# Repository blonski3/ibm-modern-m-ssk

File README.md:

# IBM Model M SSK Wireless
*Opracowanie i wykonanie układu sterującego klawiaturą mechaniczną*. Bezprzewodowa modernizacja IBM Model M SSK: nRF52840 + nPM1300, własna membrana FPC z diodą na klawisz, firmware ZMK.

## Struktura repozytorium

```
hardware/controller/   projekt KiCad 10: motherboard + daughterboard (jedna PCB, DB wyłamywany)
hardware/membrane/     projekt KiCad 10: membrana FPC, schemat matrycy 6 × 17 i obrys bazowy
hardware/membrane-row/ folia ROW (górna, 2 warstwy, diody), wersja zamówiona 2026-11-23
hardware/membrane-col/ folia COL (dolna, 1 warstwa), wersja zamówiona 2026-11-23
hardware/lib/          wspólna biblioteka: symbole, footprinty, modele 3D
production/            zamrożone paczki zamówień (controller/revA-2026-11-16: Gerbery, BOM, CPL; membrane/2026-11-23: Gerbery folii)
docs/                  CHANGELOG.md, HARDWARE_DECISIONS.md, datasheets/, diagrams/
mechanics/             pomiary i eksporty z Onshape
reference/             projekty referencyjne (Nordic, FSSK v1.00)
tools/                 własne wtyczki KiCada (*-o-matic, via-o-tronic) i skrypty (kicad-check.sh, check_3d_paths.py); indeks w tools/README.md
```

Decyzje projektowe i ich uzasadnienia: `docs/HARDWARE_DECISIONS.md`; historia zmian: `docs/CHANGELOG.md`.

## Resources

[Bolt Mod, A Comprehensive Tutorial: IBM Model M SSK 1991](https://imgur.com/gallery/bolt-mod-comprehensive-tutorial-ibm-model-m-ssk-1991-arUYken)

[FSSK v1.00 - Installation & Users Manual](https://deskthority.net/viewtopic.php?t=13551)

[Request for Permission to Integrate Zephyr PF1550 PMIC Drivers into ZMK #2958](https://github.com/zmkfirmware/zmk/issues/2958)

[nRF52840 Product Specification v1.5](https://docs.nordicsemi.com/viewer/book-attachment/de~7rocmcN70bRHnA4~zJA/H1GC97m6GZQEaMxKCN6OOg-de~7rocmcN70bRHnA4~zJA)

[nPM1300 Product Specification v1.3](https://docs.nordicsemi.com/viewer/book-attachment/ZO1FVHHS04YNNMSlbsZ0Kg/KbFbu1gXgIMOyTgBK7q46A-ZO1FVHHS04YNNMSlbsZ0Kg)

[Keyboard Layout Editor NG - IBM Model M](https://editor.keyboard-tools.xyz/#share=NobwRAhgrgLgFgewE5gFxgEYBsEDswA0YuEAtgKZpgCSAQgLIAEAyswNKP0IAm5WnhMAGcADhADGAS1wBzAPoBPNACYADADoAHABYAvgVCQ0q-WELgAHmgCMpwfaLmwV1BoCsdx17MFLx9R7eDj5+rgGePmYAugbgSqi2QUmRwanJDqHW4ekxhgDuNtkp6SXFZU4FCUVOLu4R9rnglVkA7IHlpWkdTSrqyu1gjWCVyn0DnRPFPVVtnqGjA0PN1b7ONkTL49Mtc8OFW2sJG-u7tSspQy7Wo21E8QC0AMy7y-12S4VvQUMPysdVi1ih2sekclxs2juaHuoOiUSAA)

[WR-PHD Pin Header drawing](https://www.we-online.com/components/products/datasheet/61300811021.pdf)

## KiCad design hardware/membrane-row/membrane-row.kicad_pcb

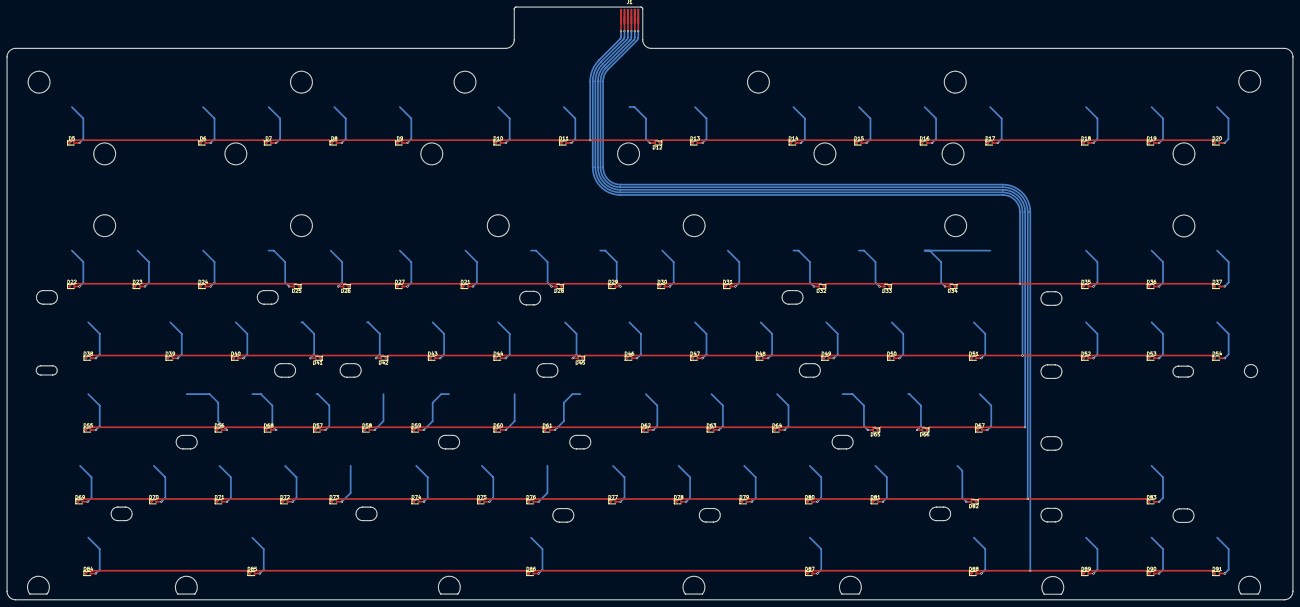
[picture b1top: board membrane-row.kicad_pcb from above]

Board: 2 copper layers, 373.4 x 172.1 mm, 176 parts (0 on the bottom side), 93 nets.

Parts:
D5, D6, D7, D8, D9, D10, D11, D12, D13, D14, D15, D16, D17, D18, D19, D20, D21, D22, D23, D24, D25, D26, D27, D28, D29, D30, D31, D32, D33, D34, D35, D36, D37, D38, D39, D40, D41, D42, D43, D44, D45, D46, D47, D48, D49, D50, D51, D52, D53, D54, D55, D56, D57, D58, D59, D60, D61, D62, D63, D64, D65, D66, D67, D68, D69, D70, D71, D72, D73, D74, D75, D76, D77, D78, D79, D80, D81, D82, D83, D84, D85, D86, D87, D88, D89, D90, D91: D_Small_Filled; D_SOD-523
J1: Conn_01x06; FFC_solder_6P_P1.00
SW1: Esc; ibm_bs_1u_row
SW2: F1; ibm_bs_1u_row
SW3: F2; ibm_bs_1u_row
SW4: F3; ibm_bs_1u_row
SW5: F4; ibm_bs_1u_row
SW6: F5; ibm_bs_1u_row
SW7: F6; ibm_bs_1u_row
SW8: F7; ibm_bs_1u_row
SW9: F8; ibm_bs_1u_row
SW10: F9; ibm_bs_1u_row
SW11: F10; ibm_bs_1u_row
SW12: F11; ibm_bs_1u_row
SW13: F12; ibm_bs_1u_row
SW14: PrintScreen; ibm_bs_1u_row
SW15: ScrollLock; ibm_bs_1u_row
SW16: PauseBreak; ibm_bs_1u_row
SW17, SW31: Backspace; ibm_bs_1u_row
SW18: ibm_bs_1u_row
SW19: 1; ibm_bs_1u_row
SW20: 2; ibm_bs_1u_row
SW21: 3; ibm_bs_1u_row
SW22: 4; ibm_bs_1u_row
SW23: 5; ibm_bs_1u_row
SW24: 6; ibm_bs_1u_row
SW25: 7; ibm_bs_1u_row
SW26: 8; ibm_bs_1u_row
SW27: 9; ibm_bs_1u_row
SW28: 0; ibm_bs_1u_row
SW29: -; ibm_bs_1u_row
SW30: =; ibm_bs_1u_row
SW32: Insert; ibm_bs_1u_row
SW33: Home; ibm_bs_1u_row
SW34: PgUp; ibm_bs_1u_row
SW35: Tab; ibm_bs_1u_row
SW36: Q; ibm_bs_1u_row
SW37: W; ibm_bs_1u_row
SW38: E; ibm_bs_1u_row
SW39: R; ibm_bs_1u_row
SW40: T; ibm_bs_1u_row
SW41: Y; ibm_bs_1u_row
SW42: U; ibm_bs_1u_row
SW43: I; ibm_bs_1u_row
SW44: O; ibm_bs_1u_row
SW45: P; ibm_bs_1u_row
SW46: [; ibm_bs_1u_row
SW47: ]; ibm_bs_1u_row
SW48: \; ibm_bs_1u_row
SW49: Delete; ibm_bs_1u_row
SW50: End; ibm_bs_1u_row
SW51: PgDw; ibm_bs_1u_row
SW52: CapsLock; ibm_bs_1u_row
SW53: A; ibm_bs_1u_row
SW54: S; ibm_bs_1u_row
SW55: D; ibm_bs_1u_row
SW56: F; ibm_bs_1u_row
SW57: G; ibm_bs_1u_row
SW58: H; ibm_bs_1u_row
SW59: J; ibm_bs_1u_row
SW60: K; ibm_bs_1u_row
SW61: L; ibm_bs_1u_row
SW62: ;; ibm_bs_1u_row
SW63: '; ibm_bs_1u_row
SW64, SW67: \ ISO; ibm_bs_1u_row
SW65: Enter; ibm_bs_1u_row
SW66: LShift; ibm_bs_1u_row
SW68: Z; ibm_bs_1u_row
SW69: X; ibm_bs_1u_row
SW70: C; ibm_bs_1u_row
SW71: V; ibm_bs_1u_row
SW72: B; ibm_bs_1u_row
SW73: N; ibm_bs_1u_row
SW74: M; ibm_bs_1u_row
SW75: ,; ibm_bs_1u_row
SW76: .; ibm_bs_1u_row
SW77: /; ibm_bs_1u_row
SW78: RShift (???); ibm_bs_1u_row
SW79: RShift; ibm_bs_1u_row
SW80: Up; ibm_bs_1u_row
SW81: LCtrl; ibm_bs_1u_row
SW82: LAlt; ibm_bs_1u_row
SW83: Space; ibm_bs_1u_row
SW84: RAlt; ibm_bs_1u_row
SW85: RCtrl; ibm_bs_1u_row
SW86: Left; ibm_bs_1u_row
SW87: Down; ibm_bs_1u_row
SW88: Right; ibm_bs_1u_row

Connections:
/ROW0: D5.1 (K), D6.1 (K), D7.1 (K), D8.1 (K), D9.1 (K), D10.1 (K), D11.1 (K), D12.1 (K), D13.1 (K), D14.1 (K), D15.1 (K), D16.1 (K), D17.1 (K), D18.1 (K), D19.1 (K), D20.1 (K), J1.6
/ROW1: D21.1 (K), D22.1 (K), D23.1 (K), D24.1 (K), D25.1 (K), D26.1 (K), D27.1 (K), D28.1 (K), D29.1 (K), D30.1 (K), D31.1 (K), D32.1 (K), D33.1 (K), D34.1 (K), D35.1 (K), D36.1 (K), D37.1 (K), J1.5
/ROW2: D38.1 (K), D39.1 (K), D40.1 (K), D41.1 (K), D42.1 (K), D43.1 (K), D44.1 (K), D45.1 (K), D46.1 (K), D47.1 (K), D48.1 (K), D49.1 (K), D50.1 (K), D51.1 (K), D52.1 (K), D53.1 (K), D54.1 (K), J1.4
/ROW3: D55.1 (K), D56.1 (K), D57.1 (K), D58.1 (K), D59.1 (K), D60.1 (K), D61.1 (K), D62.1 (K), D63.1 (K), D64.1 (K), D65.1 (K), D66.1 (K), D67.1 (K), D68.1 (K), J1.3
/ROW4: D69.1 (K), D70.1 (K), D71.1 (K), D72.1 (K), D73.1 (K), D74.1 (K), D75.1 (K), D76.1 (K), D77.1 (K), D78.1 (K), D79.1 (K), D80.1 (K), D81.1 (K), D82.1 (K), D83.1 (K), J1.2
/ROW5: D84.1 (K), D85.1 (K), D86.1 (K), D87.1 (K), D88.1 (K), D89.1 (K), D90.1 (K), D91.1 (K), J1.1
unnamed: D5.2 (A), SW1.1 (1_1)
unnamed: D6.2 (A), SW2.1 (1_1)
unnamed: D7.2 (A), SW3.1 (1_1)
unnamed: D8.2 (A), SW4.1 (1_1)
unnamed: D9.2 (A), SW5.1 (1_1)
unnamed: D10.2 (A), SW6.1 (1_1)
unnamed: D11.2 (A), SW7.1 (1_1)
unnamed: D12.2 (A), SW8.1 (1_1)
unnamed: D13.2 (A), SW9.1 (1_1)
unnamed: D14.2 (A), SW10.1 (1_1)
unnamed: D15.2 (A), SW11.1 (1_1)
unnamed: D16.2 (A), SW12.1 (1_1)
unnamed: D17.2 (A), SW13.1 (1_1)
unnamed: D18.2 (A), SW14.1 (1_1)
unnamed: D19.2 (A), SW15.1 (1_1)
unnamed: D20.2 (A), SW16.1 (1_1)
unnamed: D21.2 (A), SW24.1 (1_1)
unnamed: D22.2 (A), SW18.1 (1_1)
unnamed: D23.2 (A), SW19.1 (1_1)
unnamed: D24.2 (A), SW20.1 (1_1)
unnamed: D25.2 (A), SW21.1 (1_1)
unnamed: D26.2 (A), SW22.1 (1_1)
unnamed: D27.2 (A), SW23.1 (1_1)
unnamed: D28.2 (A), SW25.1 (1_1)
unnamed: D29.2 (A), SW26.1 (1_1)
unnamed: D30.2 (A), SW27.1 (1_1)
unnamed: D31.2 (A), SW28.1 (1_1)
unnamed: D32.2 (A), SW29.1 (1_1)
unnamed: D33.2 (A), SW30.1 (1_1)
unnamed: D34.2 (A), SW17.1 (1_1), SW31.1 (1_1)
unnamed: D35.2 (A), SW32.1 (1_1)
unnamed: D36.2 (A), SW33.1 (1_1)
unnamed: D37.2 (A), SW34.1 (1_1)
unnamed: D38.2 (A), SW35.1 (1_1)
unnamed: D39.2 (A), SW36.1 (1_1)
unnamed: D40.2 (A), SW37.1 (1_1)
unnamed: D41.2 (A), SW38.1 (1_1)
unnamed: D42.2 (A), SW39.1 (1_1)
unnamed: D43.2 (A), SW40.1 (1_1)
unnamed: D44.2 (A), SW41.1 (1_1)
unnamed: D45.2 (A), SW42.1 (1_1)
unnamed: D46.2 (A), SW43.1 (1_1)
unnamed: D47.2 (A), SW44.1 (1_1)
unnamed: D48.2 (A), SW45.1 (1_1)
unnamed: D49.2 (A), SW46.1 (1_1)
unnamed: D50.2 (A), SW47.1 (1_1)
unnamed: D51.2 (A), SW48.1 (1_1)
unnamed: D52.2 (A), SW49.1 (1_1)
unnamed: D53.2 (A), SW50.1 (1_1)
unnamed: D54.2 (A), SW51.1 (1_1)
unnamed: D55.2 (A), SW52.1 (1_1)
unnamed: D56.2 (A), SW53.1 (1_1)
unnamed: D57.2 (A), SW55.1 (1_1)
unnamed: D58.2 (A), SW56.1 (1_1)
unnamed: D59.2 (A), SW57.1 (1_1)
unnamed: D60.2 (A), SW58.1 (1_1)
unnamed: D61.2 (A), SW59.1 (1_1)
unnamed: D62.2 (A), SW60.1 (1_1)
unnamed: D63.2 (A), SW61.1 (1_1)
unnamed: D64.2 (A), SW62.1 (1_1)
unnamed: D65.2 (A), SW63.1 (1_1)
unnamed: D66.2 (A), SW64.1 (1_1)
unnamed: D67.2 (A), SW65.1 (1_1)
unnamed: D68.2 (A), SW54.1 (1_1)
unnamed: D69.2 (A), SW66.1 (1_1)
unnamed: D70.2 (A), SW67.1 (1_1)
unnamed: D71.2 (A), SW68.1 (1_1)
unnamed: D72.2 (A), SW69.1 (1_1)
unnamed: D73.2 (A), SW70.1 (1_1)
unnamed: D74.2 (A), SW71.1 (1_1)
unnamed: D75.2 (A), SW72.1 (1_1)
unnamed: D76.2 (A), SW73.1 (1_1)
unnamed: D77.2 (A), SW74.1 (1_1)
unnamed: D78.2 (A), SW75.1 (1_1)
unnamed: D79.2 (A), SW76.1 (1_1)
unnamed: D80.2 (A), SW77.1 (1_1)
unnamed: D81.2 (A), SW78.1 (1_1)
unnamed: D82.2 (A), SW79.1 (1_1)
unnamed: D83.2 (A), SW80.1 (1_1)
unnamed: D84.2 (A), SW81.1 (1_1)
unnamed: D85.2 (A), SW82.1 (1_1)
unnamed: D86.2 (A), SW83.1 (1_1)
unnamed: D87.2 (A), SW84.1 (1_1)
unnamed: D88.2 (A), SW85.1 (1_1)
unnamed: D89.2 (A), SW86.1 (1_1)
unnamed: D90.2 (A), SW87.1 (1_1)
unnamed: D91.2 (A), SW88.1 (1_1)

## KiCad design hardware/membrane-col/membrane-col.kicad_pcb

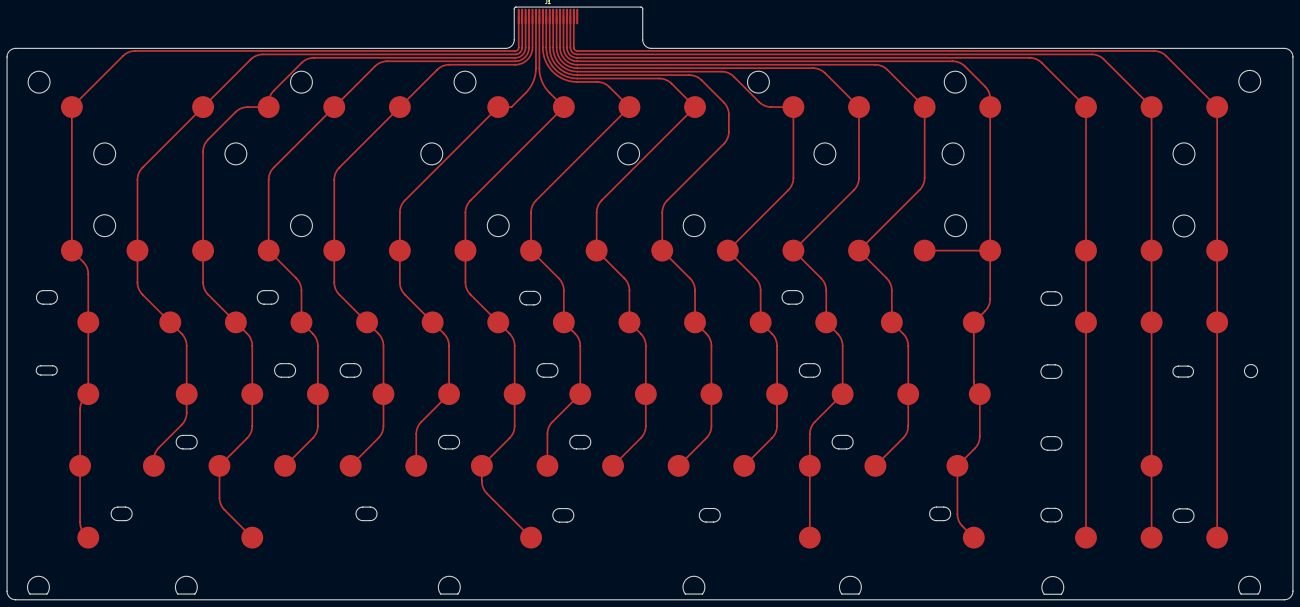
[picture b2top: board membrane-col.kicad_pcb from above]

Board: 2 copper layers, 373.4 x 172.1 mm, 89 parts (0 on the bottom side), 17 nets.

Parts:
J1: Conn_01x06; FFC_solder_18P_P1.00
SW1: Esc; ibm_bs_1u_col
SW2: F1; ibm_bs_1u_col
SW3: F2; ibm_bs_1u_col
SW4: F3; ibm_bs_1u_col
SW5: F4; ibm_bs_1u_col
SW6: F5; ibm_bs_1u_col
SW7: F6; ibm_bs_1u_col
SW8: F7; ibm_bs_1u_col
SW9: F8; ibm_bs_1u_col
SW10: F9; ibm_bs_1u_col
SW11: F10; ibm_bs_1u_col
SW12: F11; ibm_bs_1u_col
SW13: F12; ibm_bs_1u_col
SW14: PrintScreen; ibm_bs_1u_col
SW15: ScrollLock; ibm_bs_1u_col
SW16: PauseBreak; ibm_bs_1u_col
SW17, SW31: Backspace; ibm_bs_1u_col
SW18: ibm_bs_1u_col
SW19: 1; ibm_bs_1u_col
SW20: 2; ibm_bs_1u_col
SW21: 3; ibm_bs_1u_col
SW22: 4; ibm_bs_1u_col
SW23: 5; ibm_bs_1u_col
SW24: 6; ibm_bs_1u_col
SW25: 7; ibm_bs_1u_col
SW26: 8; ibm_bs_1u_col
SW27: 9; ibm_bs_1u_col
SW28: 0; ibm_bs_1u_col
SW29: -; ibm_bs_1u_col
SW30: =; ibm_bs_1u_col
SW32: Insert; ibm_bs_1u_col
SW33: Home; ibm_bs_1u_col
SW34: PgUp; ibm_bs_1u_col
SW35: Tab; ibm_bs_1u_col
SW36: Q; ibm_bs_1u_col
SW37: W; ibm_bs_1u_col
SW38: E; ibm_bs_1u_col
SW39: R; ibm_bs_1u_col
SW40: T; ibm_bs_1u_col
SW41: Y; ibm_bs_1u_col
SW42: U; ibm_bs_1u_col
SW43: I; ibm_bs_1u_col
SW44: O; ibm_bs_1u_col
SW45: P; ibm_bs_1u_col
SW46: [; ibm_bs_1u_col
SW47: ]; ibm_bs_1u_col
SW48: \; ibm_bs_1u_col
SW49: Delete; ibm_bs_1u_col
SW50: End; ibm_bs_1u_col
SW51: PgDw; ibm_bs_1u_col
SW52: CapsLock; ibm_bs_1u_col
SW53: A; ibm_bs_1u_col
SW54: S; ibm_bs_1u_col
SW55: D; ibm_bs_1u_col
SW56: F; ibm_bs_1u_col
SW57: G; ibm_bs_1u_col
SW58: H; ibm_bs_1u_col
SW59: J; ibm_bs_1u_col
SW60: K; ibm_bs_1u_col
SW61: L; ibm_bs_1u_col
SW62: ;; ibm_bs_1u_col
SW63: '; ibm_bs_1u_col
SW64, SW67: \ ISO; ibm_bs_1u_col
SW65: Enter; ibm_bs_1u_col
SW66: LShift; ibm_bs_1u_col
SW68: Z; ibm_bs_1u_col
SW69: X; ibm_bs_1u_col
SW70: C; ibm_bs_1u_col
SW71: V; ibm_bs_1u_col
SW72: B; ibm_bs_1u_col
SW73: N; ibm_bs_1u_col
SW74: M; ibm_bs_1u_col
SW75: ,; ibm_bs_1u_col
SW76: .; ibm_bs_1u_col
SW77: /; ibm_bs_1u_col
SW78: RShift (???); ibm_bs_1u_col
SW79: RShift; ibm_bs_1u_col
SW80: Up; ibm_bs_1u_col
SW81: LCtrl; ibm_bs_1u_col
SW82: LAlt; ibm_bs_1u_col
SW83: Space; ibm_bs_1u_col
SW84: RAlt; ibm_bs_1u_col
SW85: RCtrl; ibm_bs_1u_col
SW86: Left; ibm_bs_1u_col
SW87: Down; ibm_bs_1u_col
SW88: Right; ibm_bs_1u_col

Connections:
/COL0: J1.1, SW1.2 (2_2), SW18.2 (2_2), SW35.2 (2_2), SW52.2 (2_2), SW66.2 (2_2), SW81.2 (2_2)
/COL1: J1.2, SW2.2 (2_2), SW19.2 (2_2), SW36.2 (2_2), SW53.2 (2_2), SW67.2 (2_2)
/COL2: J1.3, SW3.2 (2_2), SW20.2 (2_2), SW37.2 (2_2), SW54.2 (2_2), SW68.2 (2_2), SW82.2 (2_2)
/COL3: J1.4, SW4.2 (2_2), SW21.2 (2_2), SW38.2 (2_2), SW55.2 (2_2), SW69.2 (2_2)
/COL4: J1.5, SW5.2 (2_2), SW22.2 (2_2), SW39.2 (2_2), SW56.2 (2_2), SW70.2 (2_2)
/COL5: J1.6, SW6.2 (2_2), SW23.2 (2_2), SW40.2 (2_2), SW57.2 (2_2), SW71.2 (2_2)
/COL6: J1.7, SW7.2 (2_2), SW24.2 (2_2), SW41.2 (2_2), SW58.2 (2_2), SW72.2 (2_2), SW83.2 (2_2)
/COL7: J1.8, SW8.2 (2_2), SW25.2 (2_2), SW42.2 (2_2), SW59.2 (2_2), SW73.2 (2_2)
/COL8: J1.9, SW9.2 (2_2), SW26.2 (2_2), SW43.2 (2_2), SW60.2 (2_2), SW74.2 (2_2)
/COL9: J1.10, SW27.2 (2_2), SW44.2 (2_2), SW61.2 (2_2), SW75.2 (2_2)
/COL10: J1.11, SW10.2 (2_2), SW28.2 (2_2), SW45.2 (2_2), SW62.2 (2_2), SW76.2 (2_2)
/COL11: J1.12, SW11.2 (2_2), SW29.2 (2_2), SW46.2 (2_2), SW63.2 (2_2), SW77.2 (2_2), SW84.2 (2_2)
/COL12: J1.13, SW12.2 (2_2), SW30.2 (2_2), SW47.2 (2_2), SW64.2 (2_2), SW78.2 (2_2)
/COL13: J1.14, SW13.2 (2_2), SW17.2 (2_2), SW31.2 (2_2), SW48.2 (2_2), SW65.2 (2_2), SW79.2 (2_2), SW85.2 (2_2)
/COL14: J1.15, SW14.2 (2_2), SW32.2 (2_2), SW49.2 (2_2), SW86.2 (2_2)
/COL15: J1.16, SW15.2 (2_2), SW33.2 (2_2), SW50.2 (2_2), SW80.2 (2_2), SW87.2 (2_2)
/COL16: J1.17, SW16.2 (2_2), SW34.2 (2_2), SW51.2 (2_2), SW88.2 (2_2)

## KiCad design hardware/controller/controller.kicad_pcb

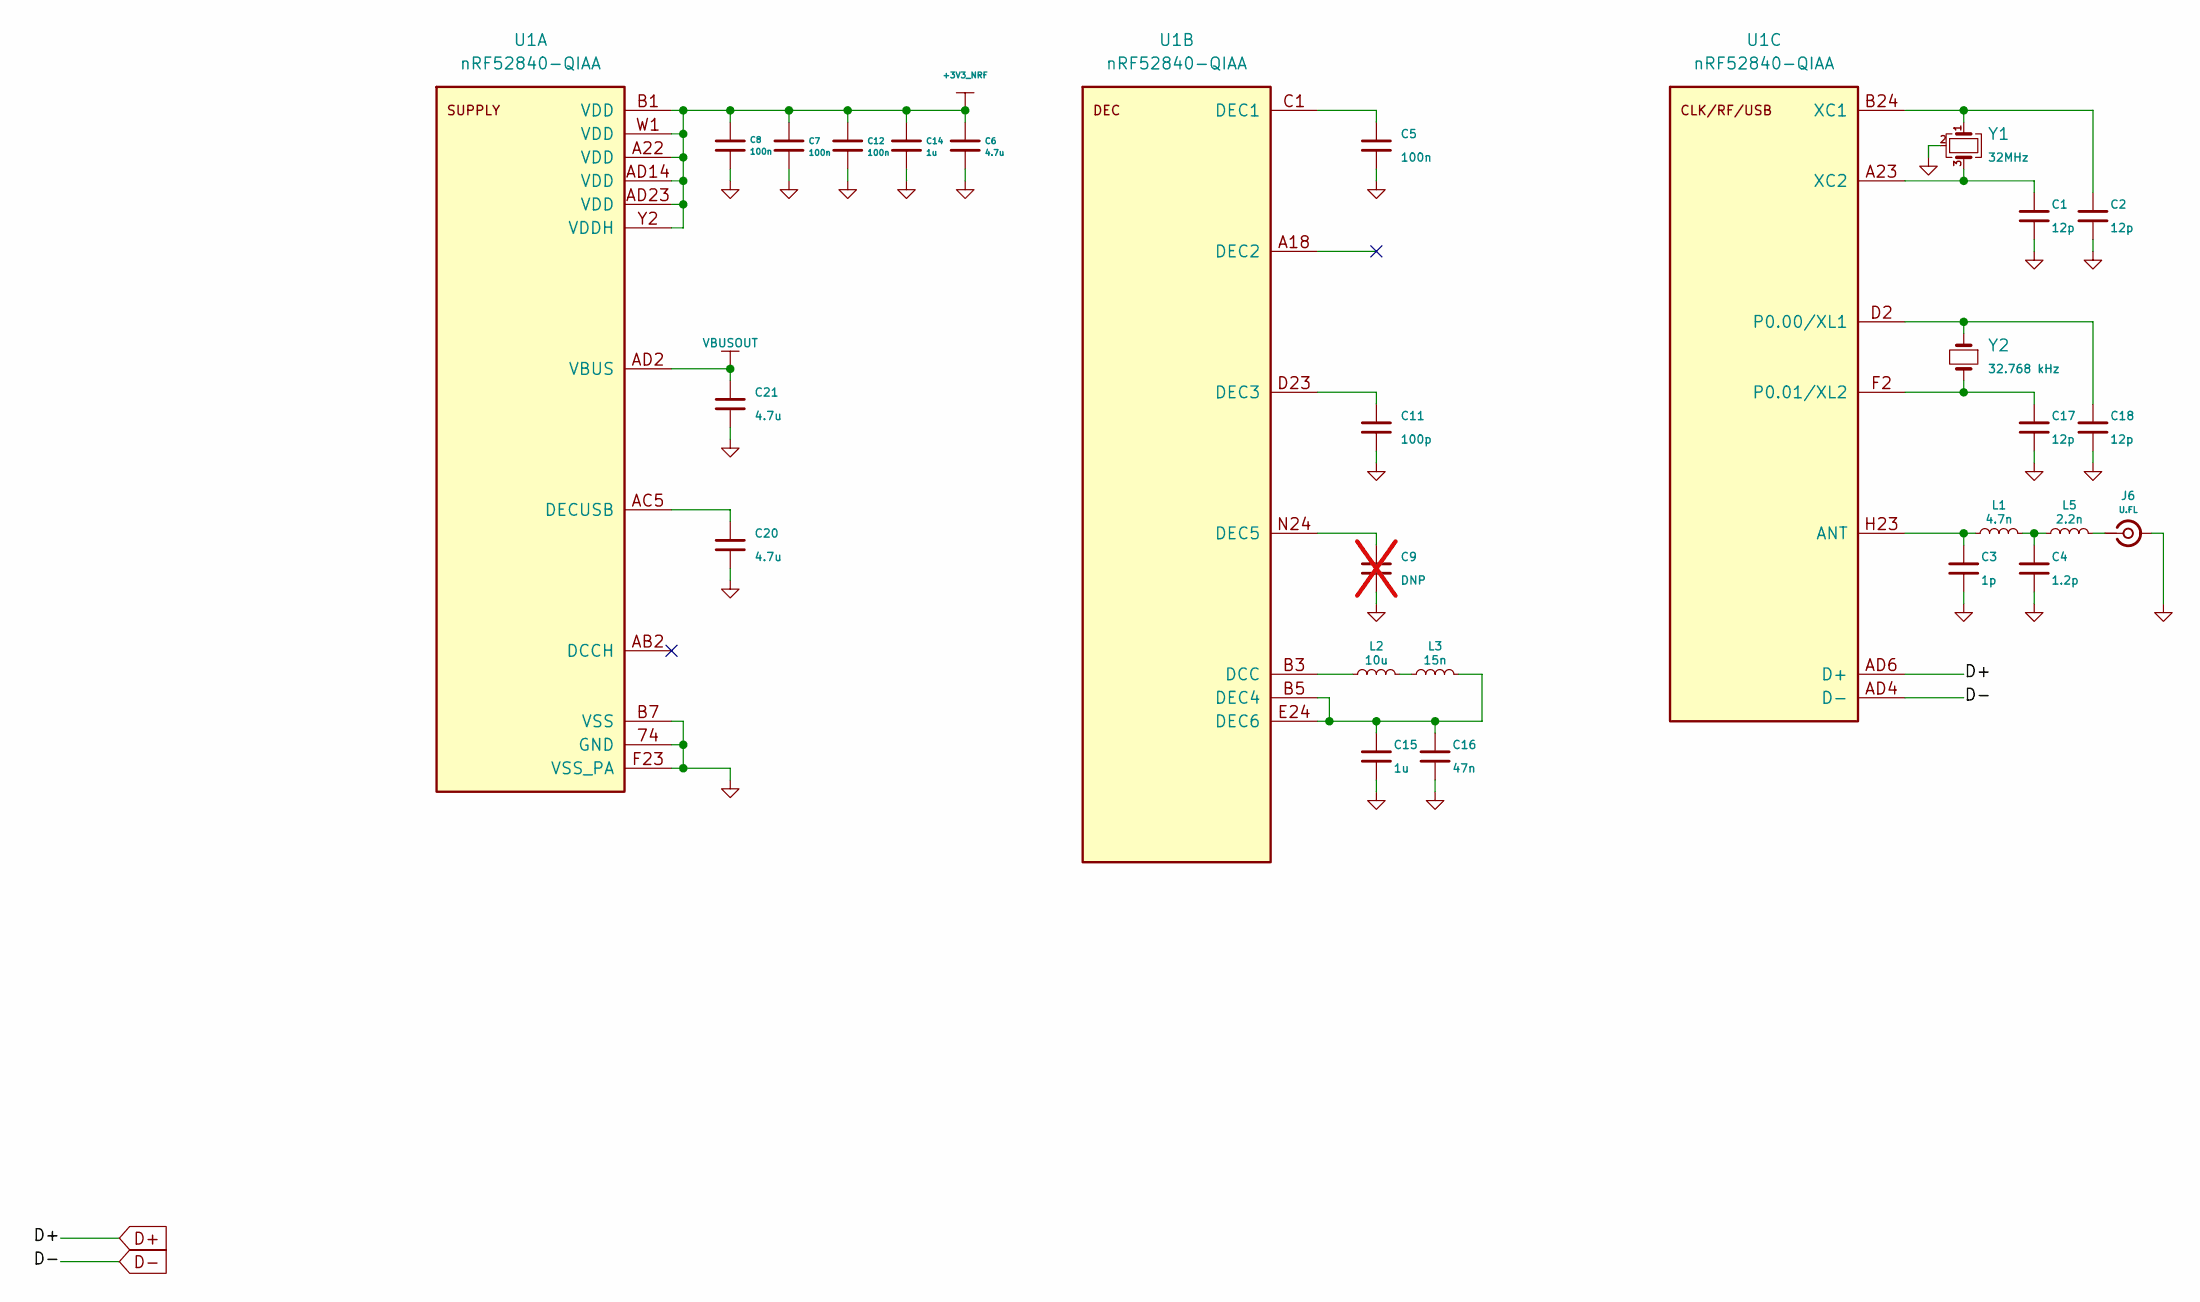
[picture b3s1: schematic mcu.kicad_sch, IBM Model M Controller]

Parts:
C1, C2, C17, C18: 12p; C_0402_1005Metric; PART NUMBER 0402CG120J500NT; LCSC Part C1547
C3: 1p; C_0402_1005Metric; PART NUMBER 0402CG1R0C500NT; LCSC Part C1550
C4: 1.2p; C_0402_1005Metric; PART NUMBER 0402CG1R2C500NT; LCSC Part C1551
C5, C7, C8, C12: 100n; C_0402_1005Metric; PART NUMBER CL05B104KO5NNNC; LCSC Part C1525
C6, C20, C21: 4.7u; C_0603_1608Metric; PART NUMBER CL10A475KO8NNNC; LCSC Part C19666
C9: DNP; C_0402_1005Metric; not fitted
C11: 100p; C_0402_1005Metric; PART NUMBER 0402CG101J500NT; LCSC Part C1546
C14, C15: 1u; C_0603_1608Metric; PART NUMBER CL10A105KB8NNNC; LCSC Part C15849
C16: 47n; C_0603_1608Metric; PART NUMBER CL10B473KB8NNNC; LCSC Part C1622
J6: U.FL; IPEX-SMD_4P-L2.6-W2.6-LS3.0_GT-RF1125A-01G; PART NUMBER U.FL-IPEX-1; LCSC Part C53433123
L1: 4.7n; L_0402_1005Metric; PART NUMBER LQG15HS4N7C02D; LCSC Part C2041409
L2: 10u; L_0603_1608Metric; LCSC Part C86083
L3: 15n; L_0402_1005Metric; LCSC Part C381880
L5: 2.2n; L_0402_1005Metric; PART NUMBER CLH1005T-2N2S-S-NP; LCSC Part C142238
U1: nRF52840-QIAA; AQFN50P700X700X85_HS-74N; PART NUMBER NRF52840-QIAA-R; LCSC Part C190794
Y1: 32MHz; Crystal_SMD_2016-4Pin_2.0x1.6mm; PART NUMBER NX2016SA-32MHZ-EXS00A-CS06654; LCSC Part C5441424
Y2: 32.768 kHz; Crystal_SMD_3215-2Pin; LCSC Part C99010

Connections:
+3V3_NRF: C6.1, C7.1, C8.1, C12.1, C14.2, U1.A22 (VDD), U1.AD14 (VDD), U1.AD23 (VDD), U1.B1 (VDD), U1.W1 (VDD), U1.Y2 (VDDH); also elsewhere on the board
D+: U1.AD6 (D+); also elsewhere on the board
D-: U1.AD4 (D-); also elsewhere on the board
GND: C1.2, C2.1, C3.2, C4.2, C5.1, C6.2, C7.2, C8.2, C9.2, C11.1, C12.2, C14.1, C15.2, C16.2, C17.2, C18.1, C20.2, C21.2, J6.2 (Ext), U1.74 (GND), U1.B7 (VSS), U1.F23 (VSS_PA), Y1.2 (G), Y1.4 (G); also elsewhere on the board
unnamed: C4.1, L1.2, L5.1
unnamed: J6.1 (In), L5.2
unnamed: L2.1, L3.2
unnamed: C20.1, U1.AC5 (DECUSB)
unnamed: L2.2, U1.B3 (DCC)
unnamed: C5.2, U1.C1 (DEC1)
unnamed: C11.2, U1.D23 (DEC3)
unnamed: C15.1, C16.1, L3.1, U1.B5 (DEC4), U1.E24 (DEC6)
unnamed: C9.1, U1.N24 (DEC5)
unnamed: C3.1, L1.1, U1.H23 (ANT)
unnamed: C18.2, U1.D2 (P0.00/XL1), Y2.1
unnamed: C17.1, U1.F2 (P0.01/XL2), Y2.2
unnamed: C2.2, U1.B24 (XC1), Y1.1
unnamed: C1.1, U1.A23 (XC2), Y1.3
VBUSOUT: C21.1, U1.AD2 (VBUS); also elsewhere on the board

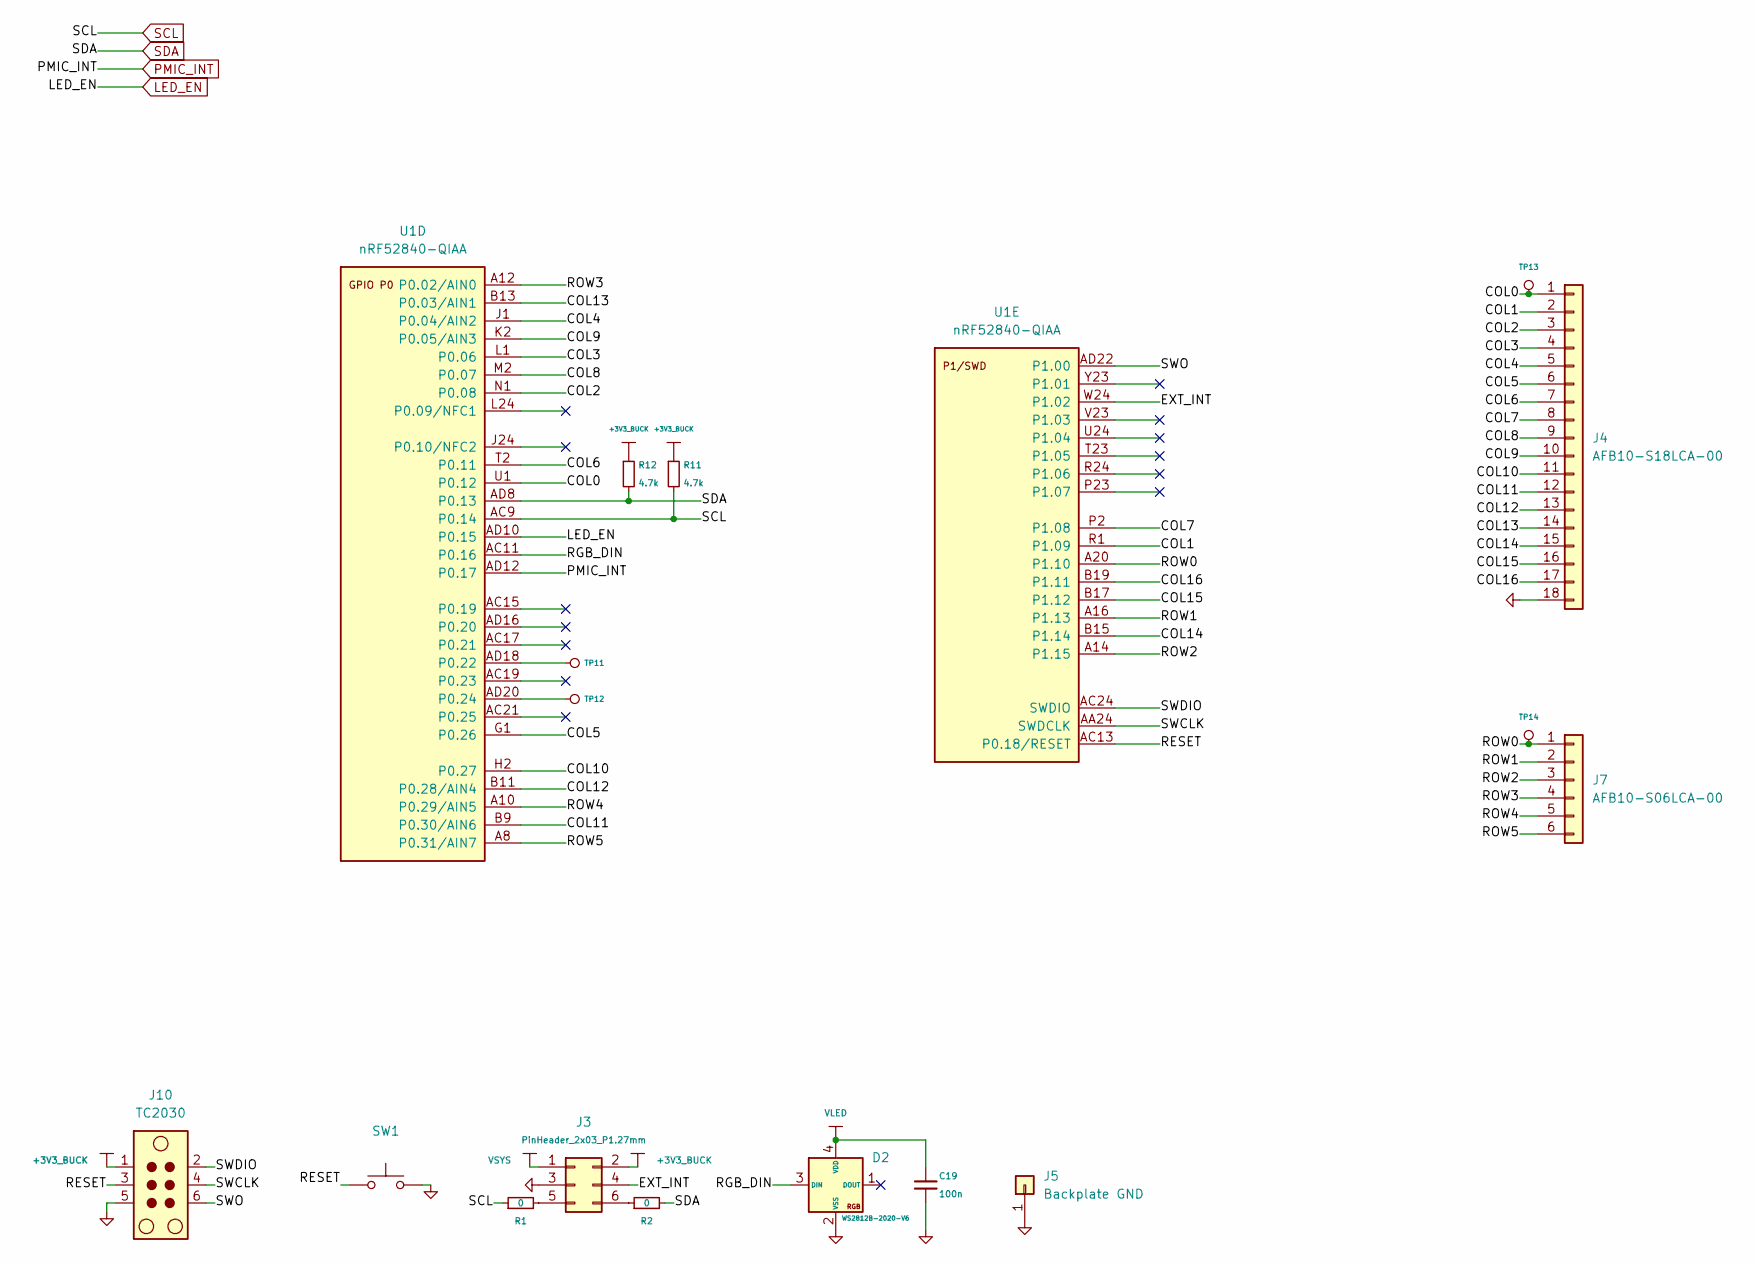
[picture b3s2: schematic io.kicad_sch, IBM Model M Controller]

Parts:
C19: 100n; C_0402_1005Metric; PART NUMBER CL05B104KO5NNNC; LCSC Part C1525
D2: WS2812B-2020-V6; LED-SMD_4P-L2.2-W2.0-P1.00_WS2815C-2020-4P; PART NUMBER WS2812B-2020-V6; LCSC Part C52917434
J3: PinHeader_2x03_P1.27mm; PinHeader_2x03_P1.27mm_Vertical_SMD
J4: AFB10-S18LCA-00; FPC-SMD_18P-P1.00_AFB10-S18LCA-00; PART NUMBER AFB10-S18LCA-00; LCSC Part C7499267
J5: Backplate GND; CONN-TH_726386-2; LCSC Part C305817
J7: AFB10-S06LCA-00; FPC-SMD_6P-P1.00_AFB10-S6LCA-00; PART NUMBER AFB10-S06LCA-00; LCSC Part C7499263
J10: TC2030; Tag-Connect_TC2030-IDC-NL_2x03_P1.27mm_Vertical
R1, R2: 0; R_0603_1608Metric; PART NUMBER 0603WAF0000T5E; LCSC Part C21189
R11, R12: 4.7k; R_0402_1005Metric; PART NUMBER 0402WGF4701TCE; LCSC Part C25900
SW1: SW_Push; SW-SMD_4P-L5.1-W5.1-P3.70-LS6.5-TL_H1.5; PART NUMBER TS-1187A-B-A-B; LCSC Part C318884
TP11, TP12: TestPoint; TestPoint_0.5
TP13, TP14: TestPoint; TestPoint_0.75
U1: nRF52840-QIAA; AQFN50P700X700X85_HS-74N; PART NUMBER NRF52840-QIAA-R; LCSC Part C190794

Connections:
+3V3_BUCK: J3.2, J10.1, R11.1, R12.1; also elsewhere on the board
/MCU IO/COL0: J4.1, TP13.1 (1_1), U1.U1 (P0.12)
/MCU IO/COL1: J4.2, U1.R1 (P1.09)
/MCU IO/COL2: J4.3, U1.N1 (P0.08)
/MCU IO/COL3: J4.4, U1.L1 (P0.06)
/MCU IO/COL4: J4.5, U1.J1 (P0.04/AIN2)
/MCU IO/COL5: J4.6, U1.G1 (P0.26)
/MCU IO/COL6: J4.7, U1.T2 (P0.11)
/MCU IO/COL7: J4.8, U1.P2 (P1.08)
/MCU IO/COL8: J4.9, U1.M2 (P0.07)
/MCU IO/COL9: J4.10, U1.K2 (P0.05/AIN3)
/MCU IO/COL10: J4.11, U1.H2 (P0.27)
/MCU IO/COL11: J4.12, U1.B9 (P0.30/AIN6)
/MCU IO/COL12: J4.13, U1.B11 (P0.28/AIN4)
/MCU IO/COL13: J4.14, U1.B13 (P0.03/AIN1)
/MCU IO/COL14: J4.15, U1.B15 (P1.14)
/MCU IO/COL15: J4.16, U1.B17 (P1.12)
/MCU IO/COL16: J4.17, U1.B19 (P1.11)
/MCU IO/EXT_INT: J3.4, U1.W24 (P1.02)
/MCU IO/RESET: J10.3, SW1.1, U1.AC13 (P0.18/RESET)
/MCU IO/RGB_DIN: D2.3 (DIN), U1.AC11 (P0.16)
/MCU IO/ROW0: J7.1, TP14.1 (1_1), U1.A20 (P1.10)
/MCU IO/ROW1: J7.2, U1.A16 (P1.13)
/MCU IO/ROW2: J7.3, U1.A14 (P1.15)
/MCU IO/ROW3: J7.4, U1.A12 (P0.02/AIN0)
/MCU IO/ROW4: J7.5, U1.A10 (P0.29/AIN5)
/MCU IO/ROW5: J7.6, U1.A8 (P0.31/AIN7)
/MCU IO/SWCLK: J10.4, U1.AA24 (SWDCLK)
/MCU IO/SWDIO: J10.2, U1.AC24 (SWDIO)
/MCU IO/SWO: J10.6, U1.AD22 (P1.00)
GND: C19.2, D2.2 (VSS), J3.3, J4.18, J5.1 (Pin_1_1), J10.5, SW1.2; also elsewhere on the board
LED_EN: U1.AD10 (P0.15); also elsewhere on the board
unnamed: J3.5, R1.2
unnamed: J3.6, R2.1
unnamed: TP11.1 (1_1), U1.AD18 (P0.22)
unnamed: TP12.1 (1_1), U1.AD20 (P0.24)
PMIC_INT: U1.AD12 (P0.17); also elsewhere on the board
SCL: R1.1, R11.2, U1.AC9 (P0.14); also elsewhere on the board
SDA: R2.2, R12.2, U1.AD8 (P0.13); also elsewhere on the board
VLED: C19.1, D2.4 (VDD); also elsewhere on the board
VSYS: J3.1; also elsewhere on the board

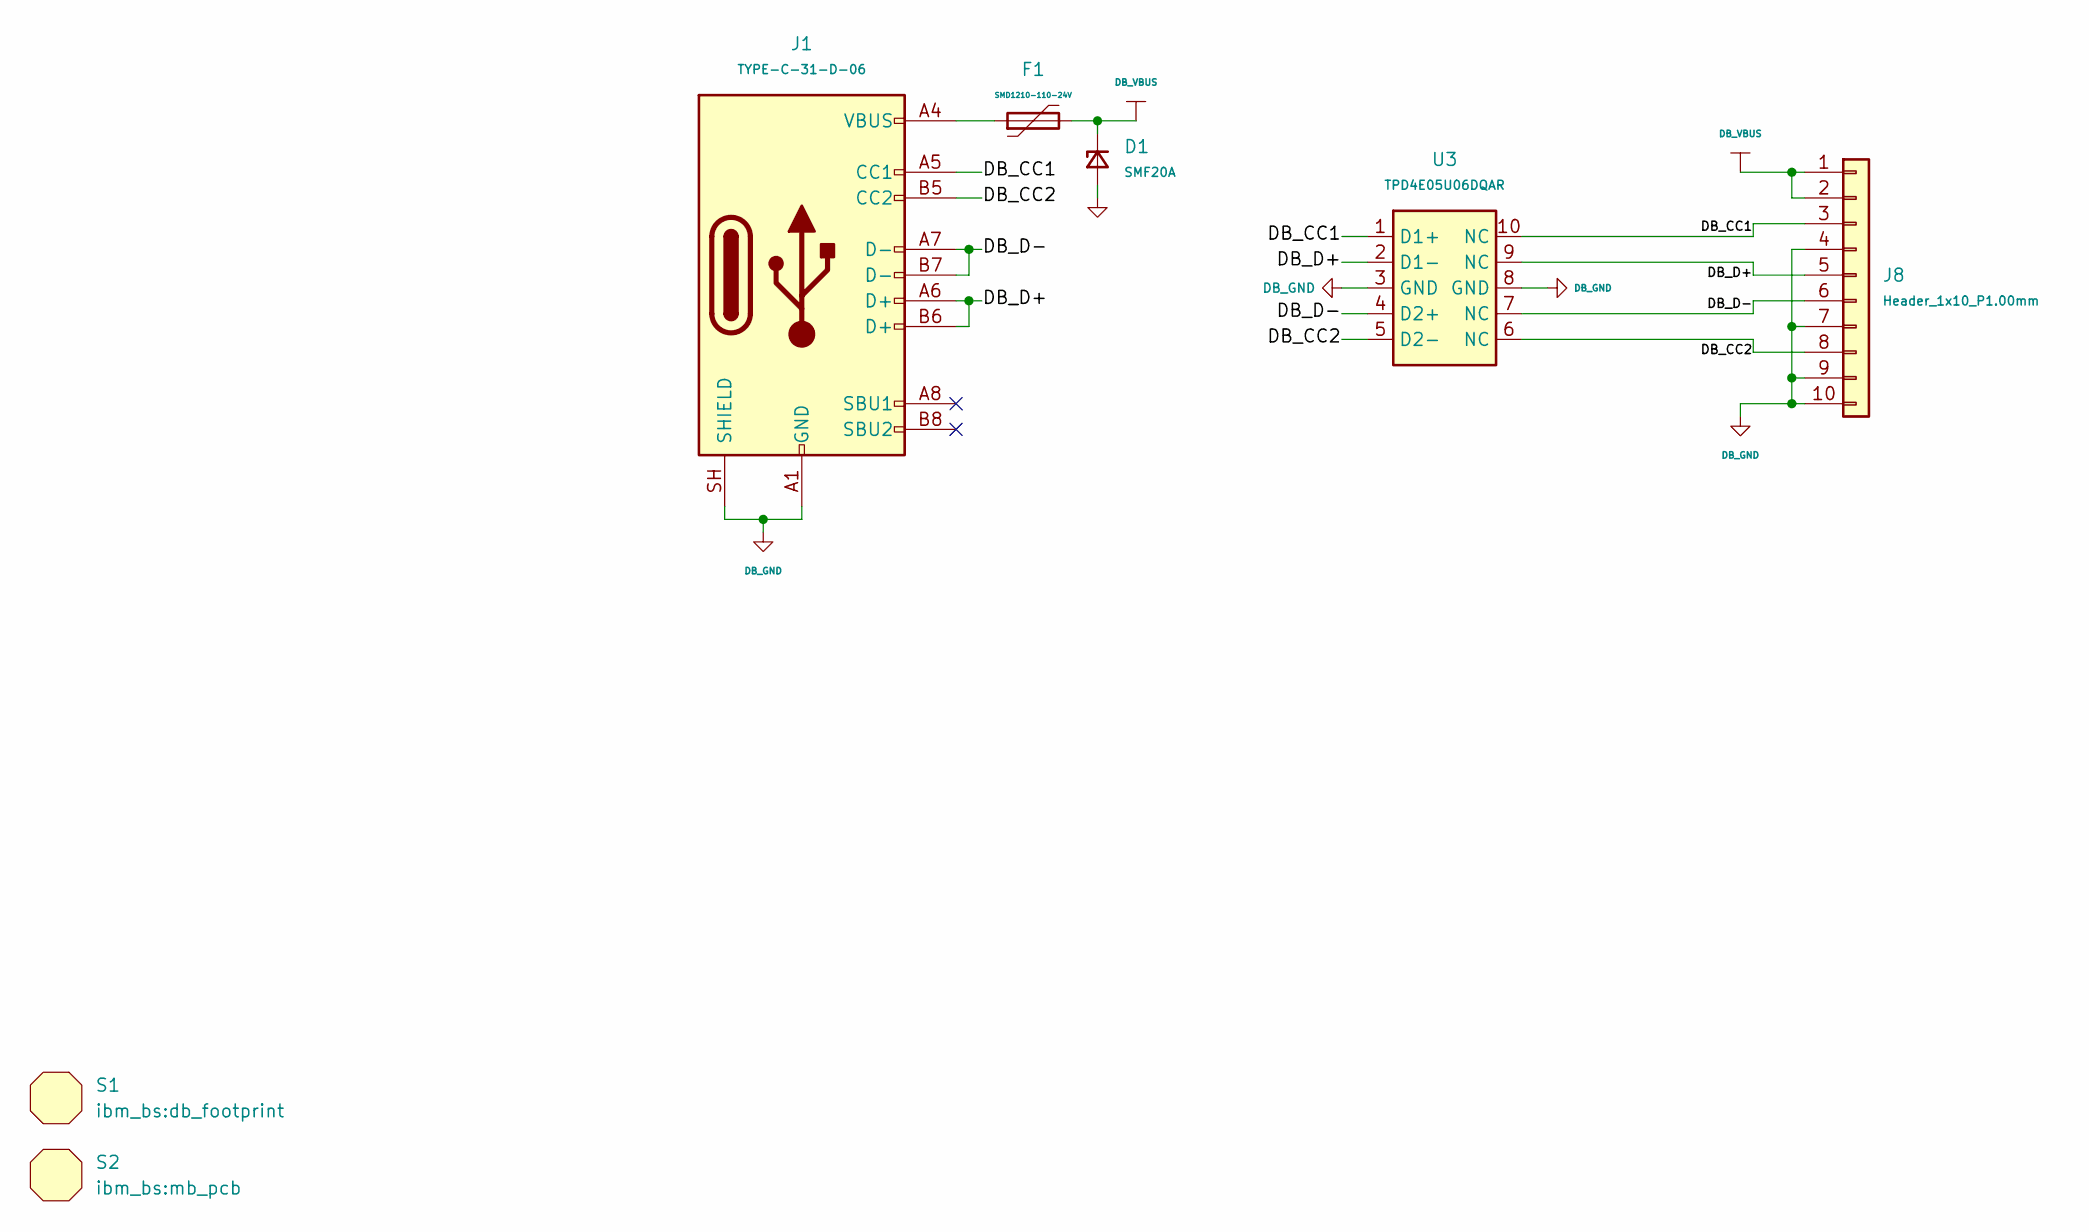
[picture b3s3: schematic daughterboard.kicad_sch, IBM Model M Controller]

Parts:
D1: SMF20A; D_SOD-123F; PART NUMBER SMF20A; LCSC Part C123788
F1: SMD1210-110-24V; Fuse_1210_3225Metric; PART NUMBER SMD1210-110-24V; LCSC Part C22436715
J1: TYPE-C-31-D-06; USB-C-SMD_TYPE-C-31-D-06; PART NUMBER TYPE-C-31-D-06; LCSC Part C2689964
J8: Header_1x10_P1.00mm; PinHeader_1x10_P1.00mm_Vertical_SMD_Pin1Left
S1: Mechanical_Shape; db_footprint
S2: Mechanical_Shape; mb_pcb
U3: TPD4E05U06DQAR; USON-10_2.5x1.0mm_P0.5mm; PART NUMBER TPD4E05U06DQAR; LCSC Part C138714

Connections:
/Daughterboard/DB_CC1: J1.A5 (CC1), J8.3, U3.1 (D1+), U3.10 (NC)
/Daughterboard/DB_CC2: J1.B5 (CC2), J8.8, U3.5 (D2-), U3.6 (NC)
/Daughterboard/DB_D+: J1.A6 (D+), J1.B6 (D+), J8.5, U3.2 (D1-), U3.9 (NC)
/Daughterboard/DB_D-: J1.A7 (D-), J1.B7 (D-), J8.6, U3.4 (D2+), U3.7 (NC)
DB_GND: D1.2 (A), J1.A1 (GND), J1.A12 (GND), J1.B1 (GND), J1.B12 (GND), J1.SH (SHIELD), J8.4, J8.7, J8.9, J8.10, U3.3 (GND), U3.8 (GND)
DB_VBUS: D1.1 (K), F1.2, J8.1, J8.2
unnamed: F1.1, J1.A4 (VBUS), J1.A9 (VBUS), J1.B4 (VBUS), J1.B9 (VBUS)
